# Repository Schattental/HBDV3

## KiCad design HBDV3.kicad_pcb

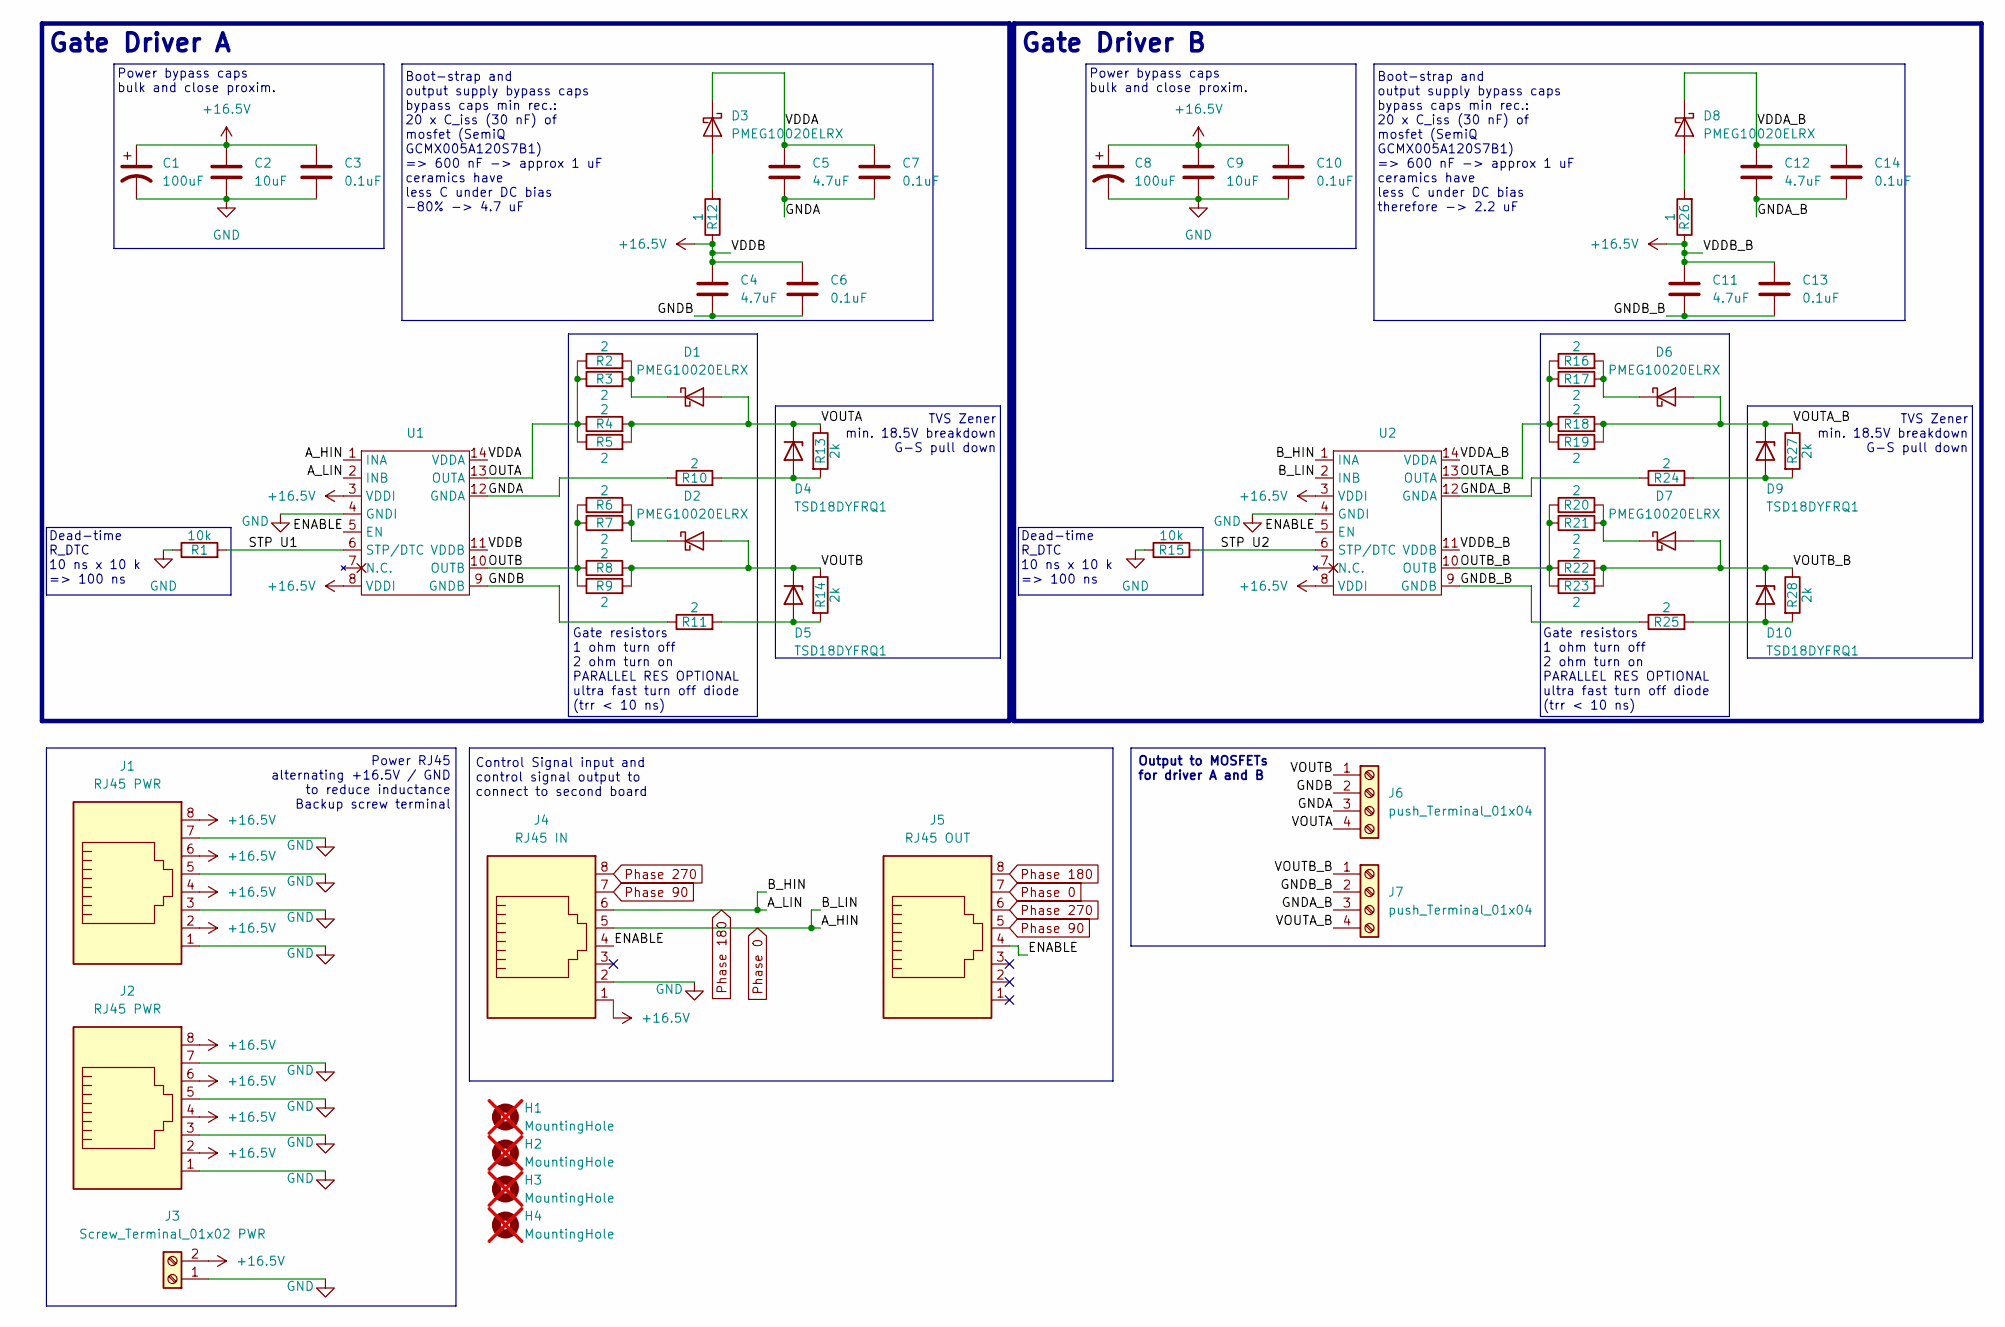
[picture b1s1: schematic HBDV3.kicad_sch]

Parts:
C1, C8: 100uF; CP_Radial_D6.3mm_H_12.5mm_P2.50mm_Würth
C2, C9: 10uF; C_0805_2012Metric_Pad1.18x1.45mm_HandSolder
C3, C6, C7, C10, C13, C14: 0.1uF; C_0805_2012Metric_Pad1.18x1.45mm_HandSolder
C4, C5, C11, C12: 4.7uF; C_0805_2012Metric_Pad1.18x1.45mm_HandSolder
D1, D2, D3, D6, D7, D8: PMEG10020ELRX; Nexperia_CFP3_SOD-123W
D4, D5, D9, D10: TSD18DYFRQ1; D_SOD-323_HandSoldering
H1, H2, H3, H4: MountingHole; MountingHole_4.3mm_M4_DIN965; not fitted
J1, J2: RJ45 PWR; RJ45_E5J8800LJG2L
J3: Screw_Terminal_01x02 PWR; Phoenix_2p_push_terminal
J4: RJ45 IN; RJ45_E5J8800LJG2L
J5: RJ45 OUT; RJ45_E5J8800LJG2L
J6, J7: push_Terminal_01x04; Phoenix_4p_push_terminal
R1, R15: 10k; R_1206_3216Metric_Pad1.30x1.75mm_HandSolder
R2, R3, R4, R5, R6, R7, R8, R9, R10, R11, R16, R17, R18, R19, R20, R21, R22, R23, R24, R25: 2; R_2512_6332Metric_Pad1.40x3.35mm_HandSolder
R12, R26: 1; R_2512_6332Metric_Pad1.40x3.35mm_HandSolder
R13, R14, R27, R28: 2k; R_1206_3216Metric_Pad1.30x1.75mm_HandSolder
U1, U2: DSO14-300mil-adapter

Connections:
+16.5V: C1.1, C2.1, C3.1, C4.1, C6.1, C8.1, C9.1, C10.1, C11.1, C13.1, J1.2, J1.4, J1.6, J1.8, J2.2, J2.4, J2.6, J2.8, J3.2, J4.1, R12.1, R26.1, U1.3 (VDDI), U1.8 (VDDI), U1.11 (VDDB), U2.3 (VDDI), U2.8 (VDDI), U2.11 (VDDB)
/ENABLE: J4.4, J5.4, U1.5 (EN), U2.5 (EN)
/GNDA: C5.2, C7.2, J6.3, R10.1, U1.12 (GNDA)
/GNDA_B: C12.2, C14.2, J7.3, R24.1, U2.12 (GNDA)
/GNDB: C4.2, C6.2, J6.2, R11.1, U1.9 (GNDB)
/GNDB_B: C11.2, C13.2, J7.2, R25.1, U2.9 (GNDB)
/OUTA: R2.1, R3.1, R4.1, R5.1, U1.13 (OUTA)
/OUTA_B: R16.1, R17.1, R18.1, R19.1, U2.13 (OUTA)
/OUTB: R6.1, R7.1, R8.1, R9.1, U1.10 (OUTB)
/OUTB_B: R20.1, R21.1, R22.1, R23.1, U2.10 (OUTB)
/STP U1: R1.2, U1.6 (STP/DTC)
/STP U2: R15.2, U2.6 (STP/DTC)
/VDDA: C5.1, C7.1, D3.1 (K), U1.14 (VDDA)
/VDDA_B: C12.1, C14.1, D8.1 (K), U2.14 (VDDA)
/VOUTA: D1.2 (A), D4.1 (K), J6.4, R4.2, R5.2, R13.1
/VOUTA_B: D6.2 (A), D9.1 (K), J7.4, R18.2, R19.2, R27.1
/VOUTB: D2.2 (A), D5.1 (K), J6.1, R8.2, R9.2, R14.1
/VOUTB_B: D7.2 (A), D10.1 (K), J7.1, R22.2, R23.2, R28.1
GND: C1.2, C2.2, C3.2, C8.2, C9.2, C10.2, J1.1, J1.3, J1.5, J1.7, J2.1, J2.3, J2.5, J2.7, J3.1, J4.2, R1.1, R15.1, U1.4 (GNDI), U2.4 (GNDI)
unnamed: D1.1 (K), R2.2, R3.2
unnamed: D2.1 (K), R6.2, R7.2
unnamed: D3.2 (A), R12.2
unnamed: D4.2 (A), R10.2, R13.2
unnamed: D5.2 (A), R11.2, R14.2
unnamed: D6.1 (K), R16.2, R17.2
unnamed: D7.1 (K), R20.2, R21.2
unnamed: D8.2 (A), R26.2
unnamed: D9.2 (A), R24.2, R27.2
unnamed: D10.2 (A), R25.2, R28.2
Phase 0: J4.5, J5.7, U1.1 (INA), U2.2 (INB)
Phase 90: J4.7, J5.5
Phase 180: J4.6, J5.8, U1.2 (INB), U2.1 (INA)
Phase 270: J4.8, J5.6

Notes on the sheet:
Power bypass caps bulk and close proxim.
Gate resistors 1 ohm turn off 2 ohm turn on PARALLEL RES OPTIONAL ultra fast turn off diode (trr < 10 ns)
Control Signal input and control signal output to connect to second board
Gate Driver B
Output to MOSFETs for driver A and B
Boot-strap and output supply bypass caps bypass caps min rec.: 20 x C_iss (30 nF) of mosfet (SemiQ GCMX005A120S7B1) => 600 nF -> approx 1 uF ceramics have less C under DC bias therefore -> 2.2 uF
Power RJ45 alternating +16.5V / GND to reduce inductance Backup screw terminal
TVS Zener min. 18.5V breakdown G-S pull down
Dead-time R_DTC 10 ns x 10 k => 100 ns
Boot-strap and output supply bypass caps bypass caps min rec.: 20 x C_iss (30 nF) of mosfet (SemiQ GCMX005A120S7B1) => 600 nF -> approx 1 uF ceramics have less C under DC bias -80% -> 4.7 uF
Gate Driver A

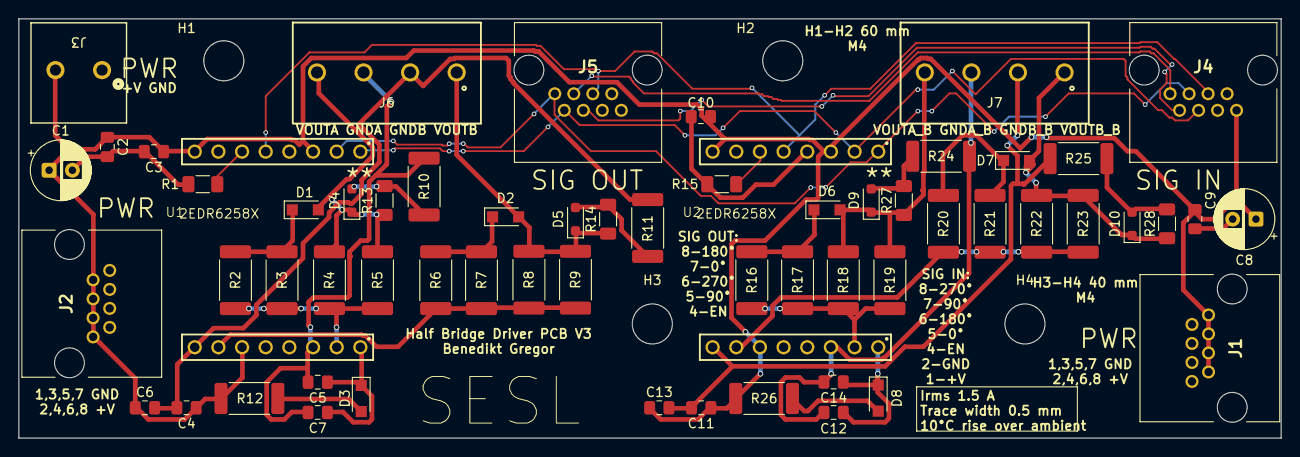
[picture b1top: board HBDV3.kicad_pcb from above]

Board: 2 copper layers, 135.5 x 45.0 mm, 65 parts (0 on the bottom side), 33 nets.

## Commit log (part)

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2026-06-29 normalize line endings
2026-06-30 big update, half done
2026-06-30 Full schematic
